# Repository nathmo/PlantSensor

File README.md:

# PlantSensor
Sensors node to monitor ambient light, temperature, humitidy, noise and soil moisture.
It it also able to drive a water pump and two light and have a LoRa transceiver to hopefully prevent my house plants from dying (among other use)
it was designed with a few use case in mind : indoor plant, outdoor plant, weather station, mailbox notifier, environemental sensor (3 I2C port that can be used for with sensors @ 3V3)
it is low power (when en deepsleep) (current draw under 50 uA@3V7 and even less at 12V)

## Features
- 3 I2C port for 3V3 peripheral (designed for OLED display, lux meter, pressure sensors)
- ambiant humidity sensors and temperature (DHT11)
- soil humidity sensors (capacitive module with analog out)
- lux meter
- pressure sensor
- microhone (detect noise level + weather / rain / wind ?)
- 3 mosftet output, max 6A total accross 3 mosfet at any time
- low power features, turn off every peripheral except ESP32 that can deepsleep and LoRa
- LoRa (433Mhz) (not compatible with TTN :( 868 Mhz is too expensive) , wifi and bluetooth connectivity
- buzzer to locate the sensors (and maybe repell some animal ?)
- GPS to track the sensors and have an accurate time base
- local data display on OLED screen or remote via the LoRa
- input voltage monitoring, get an idea of the battery left if powered by one

the PCB is 70 mm * 70 mm, i will add a better fixation system

## content
kicad schematic
BOM (20-40 CHF per unit, aliexpress as sole suplier (except PCB itself)

## futur works
- assemble and test the PCB once its manufactured
- write code to use it
- check current of the buck converter in low power mode

## firmware 
whenever the CPU come out of the sleep mode one of the following action should be performed :

mode 1)
read the config
read the sensors specified in the config
take the decision to turn on or off the mosfet if the condition set in the config are set
take the decision to display the data as specified in the config
send the data to a server if set in the config
retreive config update from the server if any and update own config or pass it to the next node

mode 2)
just transmit to any exit node the data passed uppon
applie the insctruction if we are the destination node

comming out of sleep mode are set in the config
- button action
- timer
- LoRa event

which system they trigger should also be specified in the config

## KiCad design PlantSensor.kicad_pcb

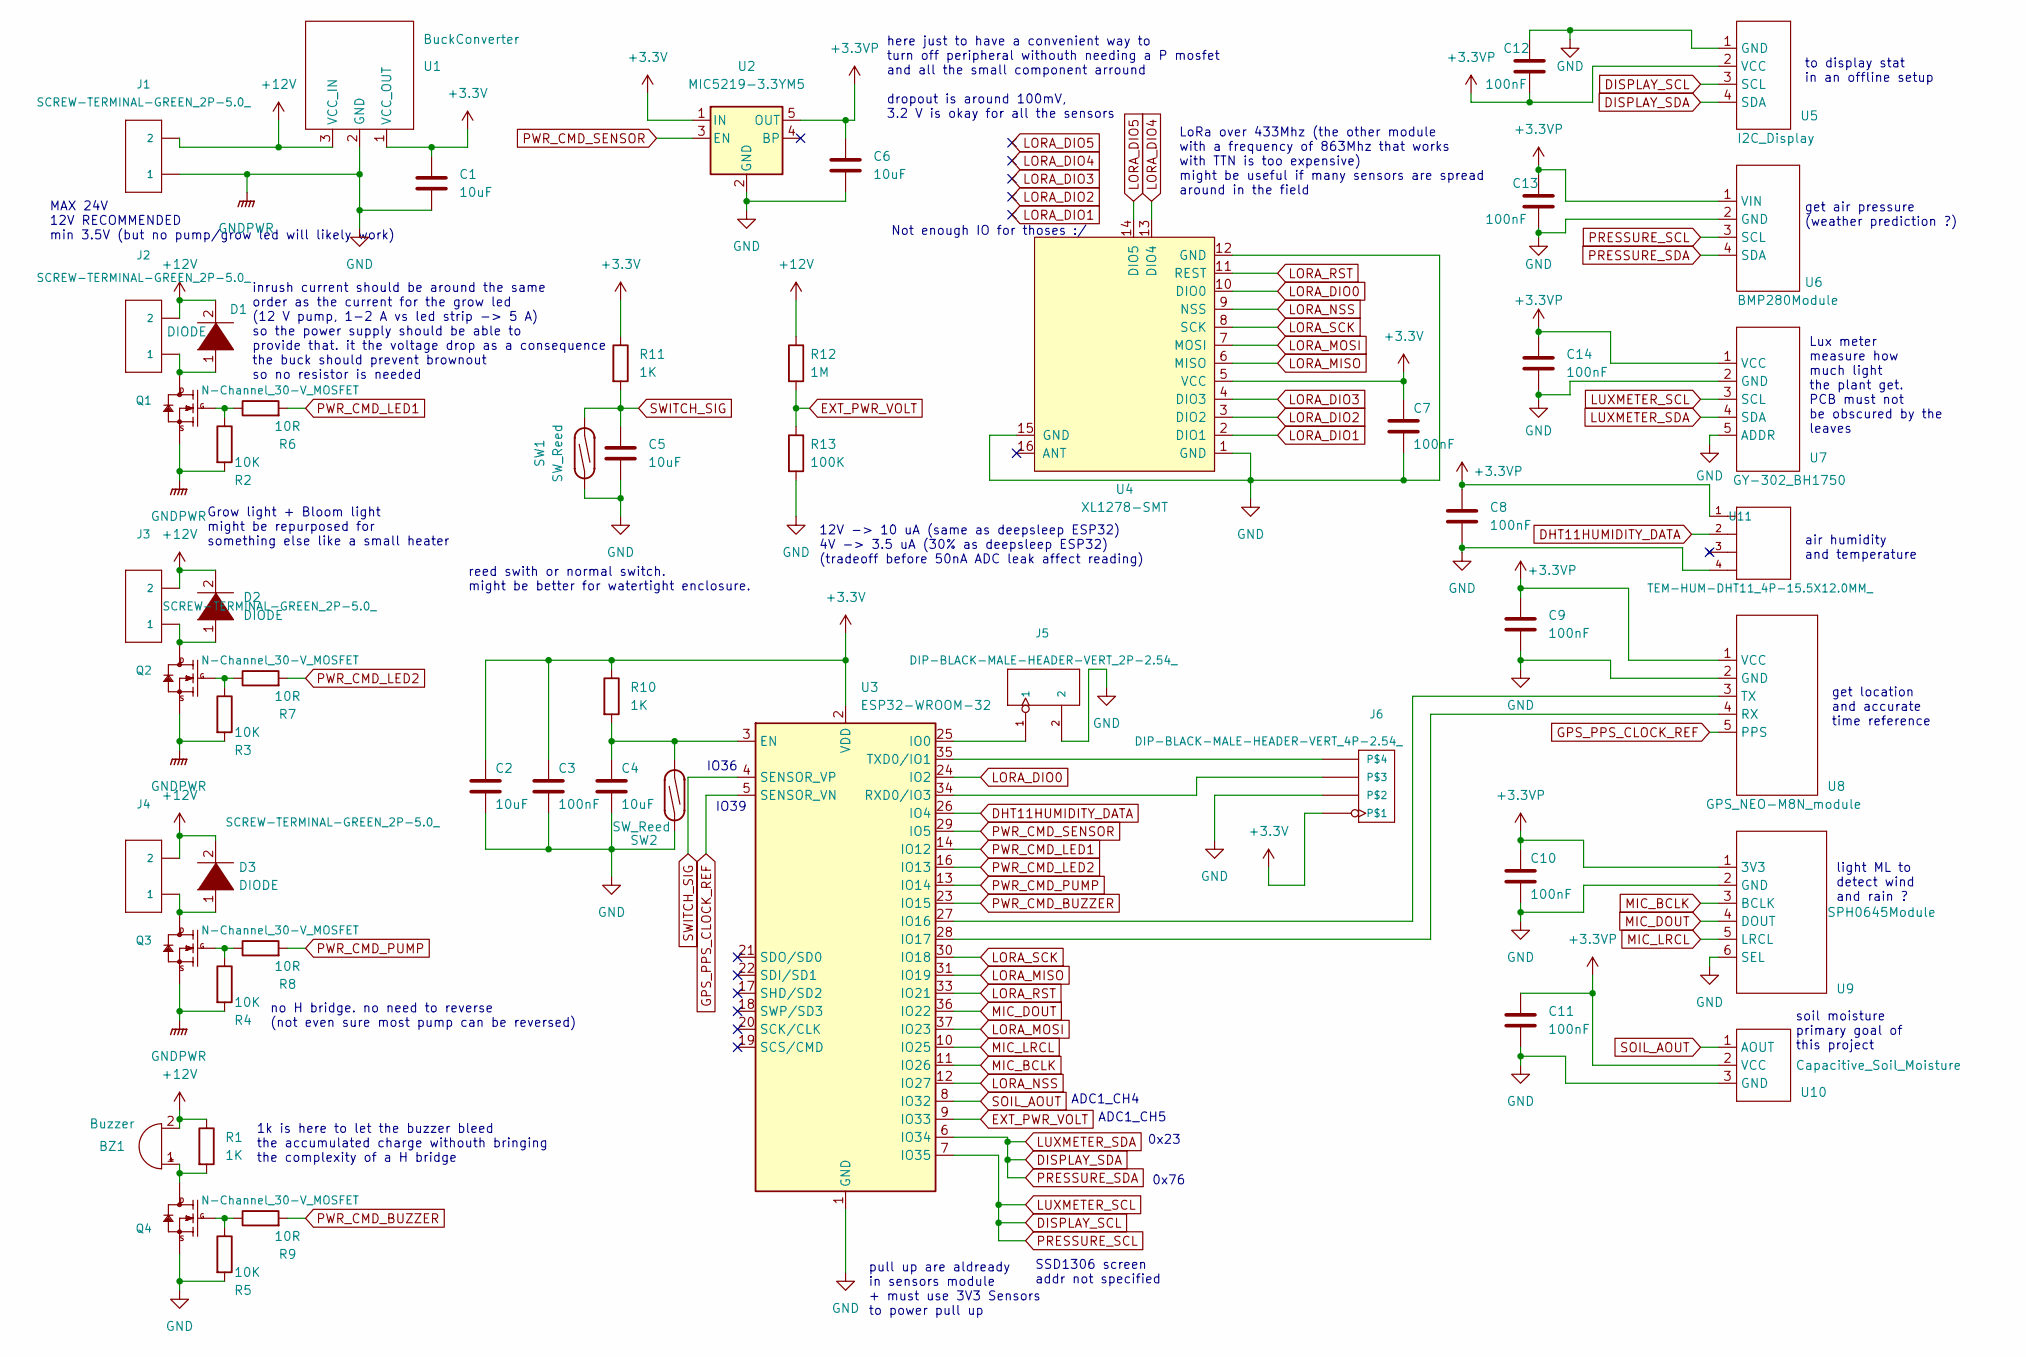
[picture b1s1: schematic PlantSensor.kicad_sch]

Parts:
BZ1: Buzzer; Buzzer_12x9.5RM7.6
C1, C2, C4, C5, C6: 10uF; C_1206_3216Metric
C3, C7, C8, C9, C10, C11, C12, C13, C14: 100nF; C_1206_3216Metric
D1, D2, D3: DIODE; D_SOD-123
J1, J2, J3, J4: SCREW-TERMINAL-GREEN_2P-5.0_; H2-5.0-10.5X8.0MM
J5: DIP-BLACK-MALE-HEADER-VERT_2P-2.54_; H2-2.54; MPN P125-1102A0BS116A1
J6: DIP-BLACK-MALE-HEADER-VERT_4P-2.54_; H4-2.54; MPN P125-1104A0BS116A1
Q1, Q2, Q3, Q4: N-Channel_30-V_MOSFET; TO-252-2
R1, R10, R11: 1K; R_1206_3216Metric
R2, R3, R4, R5: 10K; R_1206_3216Metric
R6, R7, R8, R9: 10R; R_1206_3216Metric
R12: 1M; R_1206_3216Metric
R13: 100K; R_1206_3216Metric
SW1, SW2: SW_Reed; R_Axial_DIN0207_L6.3mm_D2.5mm_P10.16mm_Horizontal
U1: BuckConverter; Buck
U2: MIC5219-3.3YM5; SOT-23-5
U3: ESP32-WROOM-32
U4: XL1278-SMT
U5: I2C_Display; Display
U6: BMP280Module
U7: GY-302_BH1750; BH1750
U8: GPS_NEO-M8N_module; GPS
U9: SPH0645Module; MicrophoneSPH0645
U10: Capacitive_Soil_Moisture; H3-2.54
U11: TEM-HUM-DHT11_4P-15.5X12.0MM_; SNR4-2.54-15.5X12.0X5.5MM; MPN DHT11

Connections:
+3.3VP: C6.1, C8.1, C9.1, C10.1, C11.1, C12.2, C13.1, C14.1, U2.5 (OUT), U5.2 (VCC), U6.1 (VIN), U7.1 (VCC), U8.1 (VCC), U9.1 (3V3), U10.2 (VCC), U11.1 (VDD)
+3V3: C1.1, C2.1, C3.1, C7.1, J6.1, R10.1, R11.1, U1.1 (VCC_OUT), U2.1 (IN), U3.2 (VDD), U4.5 (VCC)
+12V: BZ1.2 (+), D1.2 (A), D2.2 (A), D3.2 (A), J1.2, J2.2, J3.2, J4.2, R1.1, R12.1, U1.3 (VCC_IN)
DHT11HUMIDITY_DATA: U3.26 (IO4), U11.2 (DATA)
DISPLAY_SCL: U3.7 (IO35), U5.3 (SCL), U6.3 (SCL), U7.3 (SCL)
DISPLAY_SDA: U3.6 (IO34), U5.4 (SDA), U6.4 (SDA), U7.4 (SDA)
EXT_PWR_VOLT: R12.2, R13.1, U3.9 (IO33)
GND: C1.2, C2.2, C3.2, C4.2, C5.2, C6.2, C7.2, C8.2, C9.2, C10.2, C11.2, C12.1, C13.2, C14.2, J1.1, J5.2, J6.2, Q1.2 (S), Q2.2 (S), Q3.2 (S), Q4.2 (S), R2.2, R3.2, R4.2, R5.2, R13.2, SW1.1, SW2.1, U1.2 (GND), U2.2 (GND), U3.1 (GND), U3.15 (GND), U3.38 (GND), U3.39 (GND), U4.1 (GND), U4.12 (GND), U4.15 (GND), U5.1 (GND), U6.2 (GND), U7.2 (GND), U7.5 (ADDR), U8.2 (GND), U9.2 (GND), U9.6 (SEL), U10.3 (GND), U11.4 (GND)
GPS_PPS_CLOCK_REF: U3.5 (SENSOR_VN), U8.5 (PPS)
LORA_DIO0: U3.24 (IO2), U4.10 (DIO0)
LORA_DIO1: U4.2 (DIO1)
LORA_DIO2: U4.3 (DIO2)
LORA_DIO3: U4.4 (DIO3)
LORA_DIO4: U4.13 (DIO4)
LORA_DIO5: U4.14 (DIO5)
LORA_MISO: U3.31 (IO19), U4.6 (MISO)
LORA_MOSI: U3.37 (IO23), U4.7 (MOSI)
LORA_NSS: U3.12 (IO27), U4.9 (NSS)
LORA_RST: U3.33 (IO21), U4.11 (REST)
LORA_SCK: U3.30 (IO18), U4.8 (SCK)
MIC_BCLK: U3.11 (IO26), U9.3 (BCLK)
MIC_DOUT: U3.36 (IO22), U9.4 (DOUT)
MIC_LRCL: U3.10 (IO25), U9.5 (LRCL)
unnamed: BZ1.1 (-), Q4.3 (D), R1.2
unnamed: C4.1, R10.2, SW2.2, U3.3 (EN)
unnamed: D1.1 (K), J2.1, Q1.3 (D)
unnamed: D2.1 (K), J3.1, Q2.3 (D)
unnamed: D3.1 (K), J4.1, Q3.3 (D)
unnamed: J5.1, U3.25 (IO0)
unnamed: J6.3, U3.34 (RXD0/IO3)
unnamed: J6.4, U3.35 (TXD0/IO1)
unnamed: Q1.1 (G), R2.1, R6.1
unnamed: Q2.1 (G), R3.1, R7.1
unnamed: Q3.1 (G), R4.1, R8.1
unnamed: Q4.1 (G), R5.1, R9.1
unnamed: U3.27 (IO16), U8.3 (TX)
unnamed: U3.28 (IO17), U8.4 (RX)
PWR_CMD_BUZZER: R9.2, U3.23 (IO15)
PWR_CMD_LED1: R6.2, U3.14 (IO12)
PWR_CMD_LED2: R7.2, U3.16 (IO13)
PWR_CMD_PUMP: R8.2, U3.13 (IO14)
PWR_CMD_SENSOR: U2.3 (EN), U3.29 (IO5)
SOIL_AOUT: U3.8 (IO32), U10.1 (AOUT)
SWITCH_SIG: C5.1, R11.2, SW1.2, U3.4 (SENSOR_VP)

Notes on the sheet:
Not enough IO for thoses :/
Grow light + Bloom light might be repurposed for something else like a small heater
to display stat in an offline setup
air humidity and temperature
IO39
MAX 24V 12V RECOMMENDED min 3.5V (but no pump/grow led will likely work)
no H bridge. no need to reverse (not even sure most pump can be reversed)
light ML to detect wind and rain ?
LoRa over 433Mhz (the other module with a frequency of 863Mhz that works with TTN is too expensive) might be useful if many sensors are spread around in the field
soil moisture primary goal of this project
inrush current should be around the same order as the current for the grow led (12 V pump, 1-2 A vs led strip -> 5 A) so the power supply should be able to provide that. it the voltage drop as a consequence the buck should prevent brownout so no resistor is needed
Lux meter measure how much light the plant get. PCB must not be obscured by the leaves
0x76
here just to have a convenient way to turn off peripheral withouth needing a P mosfet and all the small component arround dropout is around 100mV, 3.2 V is okay for all the sensors
reed swith or normal switch. might be better for watertight enclosure.
get location and accurate time reference
1k is here to let the buzzer bleed the accumulated charge withouth bringing the complexity of a H bridge
12V -> 10 uA (same as deepsleep ESP32) 4V -> 3.5 uA (30% as deepsleep ESP32) (tradeoff before 50nA ADC leak affect reading)
ADC1_CH5
ADC1_CH4
0x23
get air pressure (weather prediction ?)
SSD1306 screen addr not specified
pull up are aldready in sensors module + must use 3V3 Sensors to power pull up
IO36

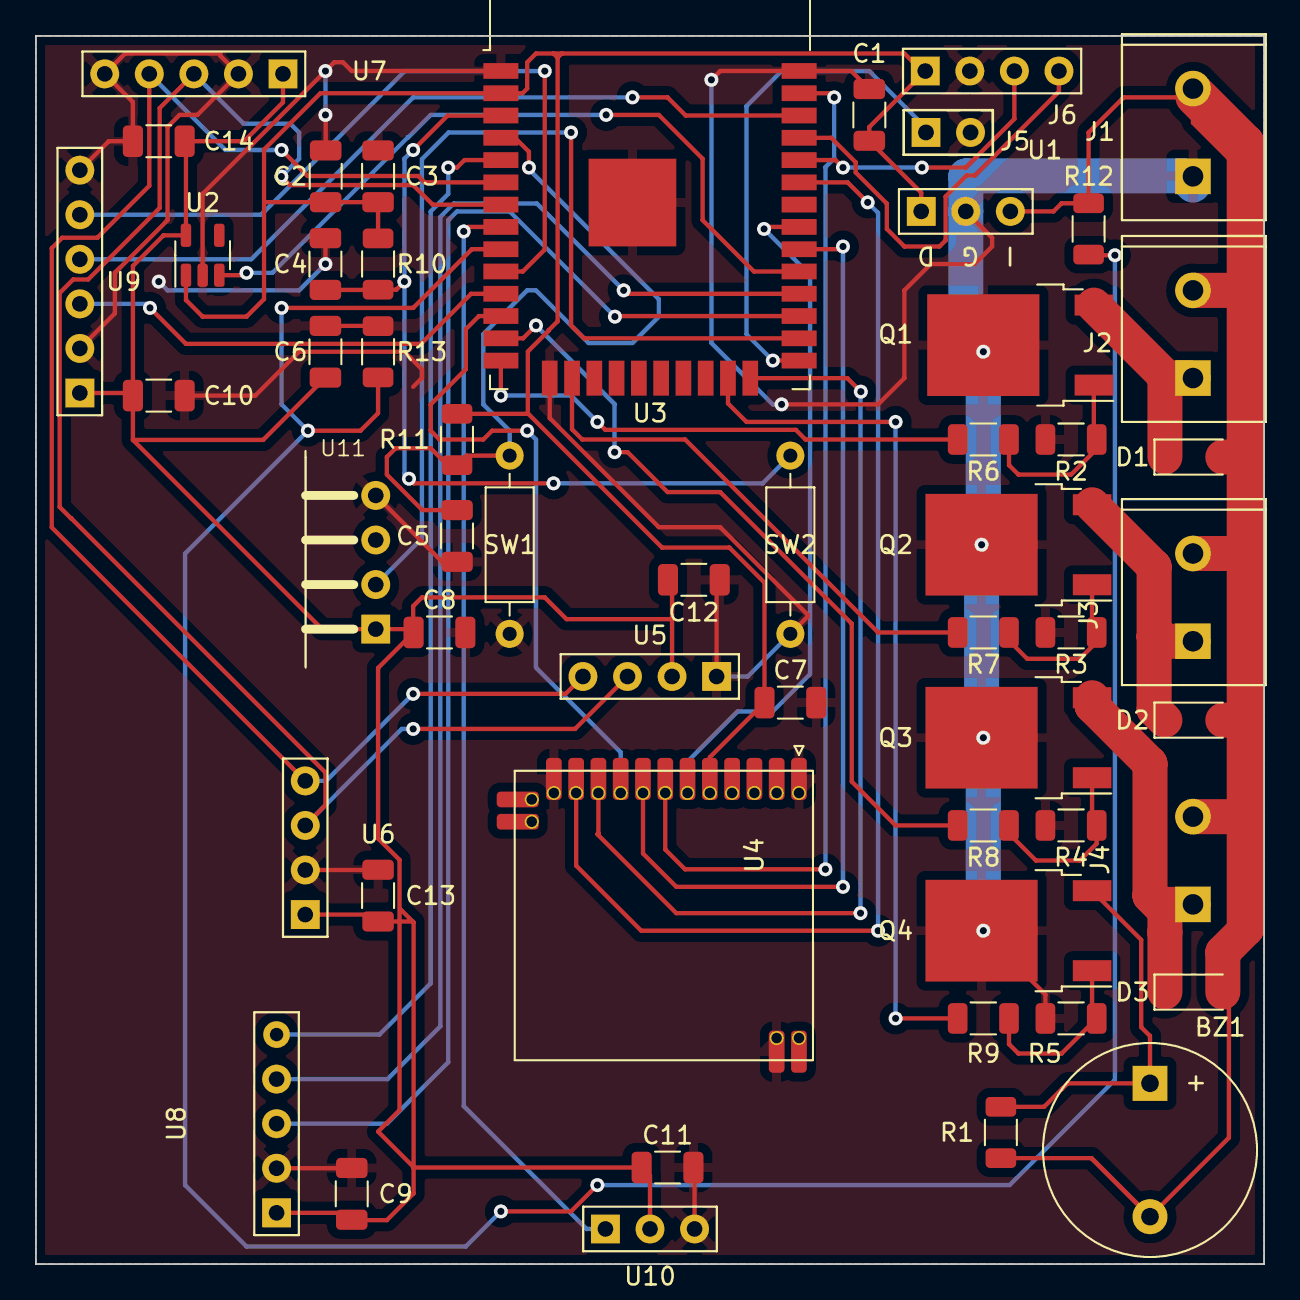
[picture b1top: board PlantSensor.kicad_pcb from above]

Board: 2 copper layers, 70.0 x 70.0 mm, 54 parts (0 on the bottom side), 39 nets.

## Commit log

2022-06-13 adding componenet library
2022-06-13 added a libriray with every used component and +
    must be extracted before usage
2022-06-15 fixed trace size + diode to prevent inductive load from damaging the mosfet
2022-06-19 small improuvment
    added mounting hole
    improved silk screen
    generated gerber for manufacturing
2022-06-19 updated 3D render
2022-07-09 asdasdtest
